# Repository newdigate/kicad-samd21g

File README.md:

# kicad-samd21g
generic samd21g18a board based on arduino mkrzero

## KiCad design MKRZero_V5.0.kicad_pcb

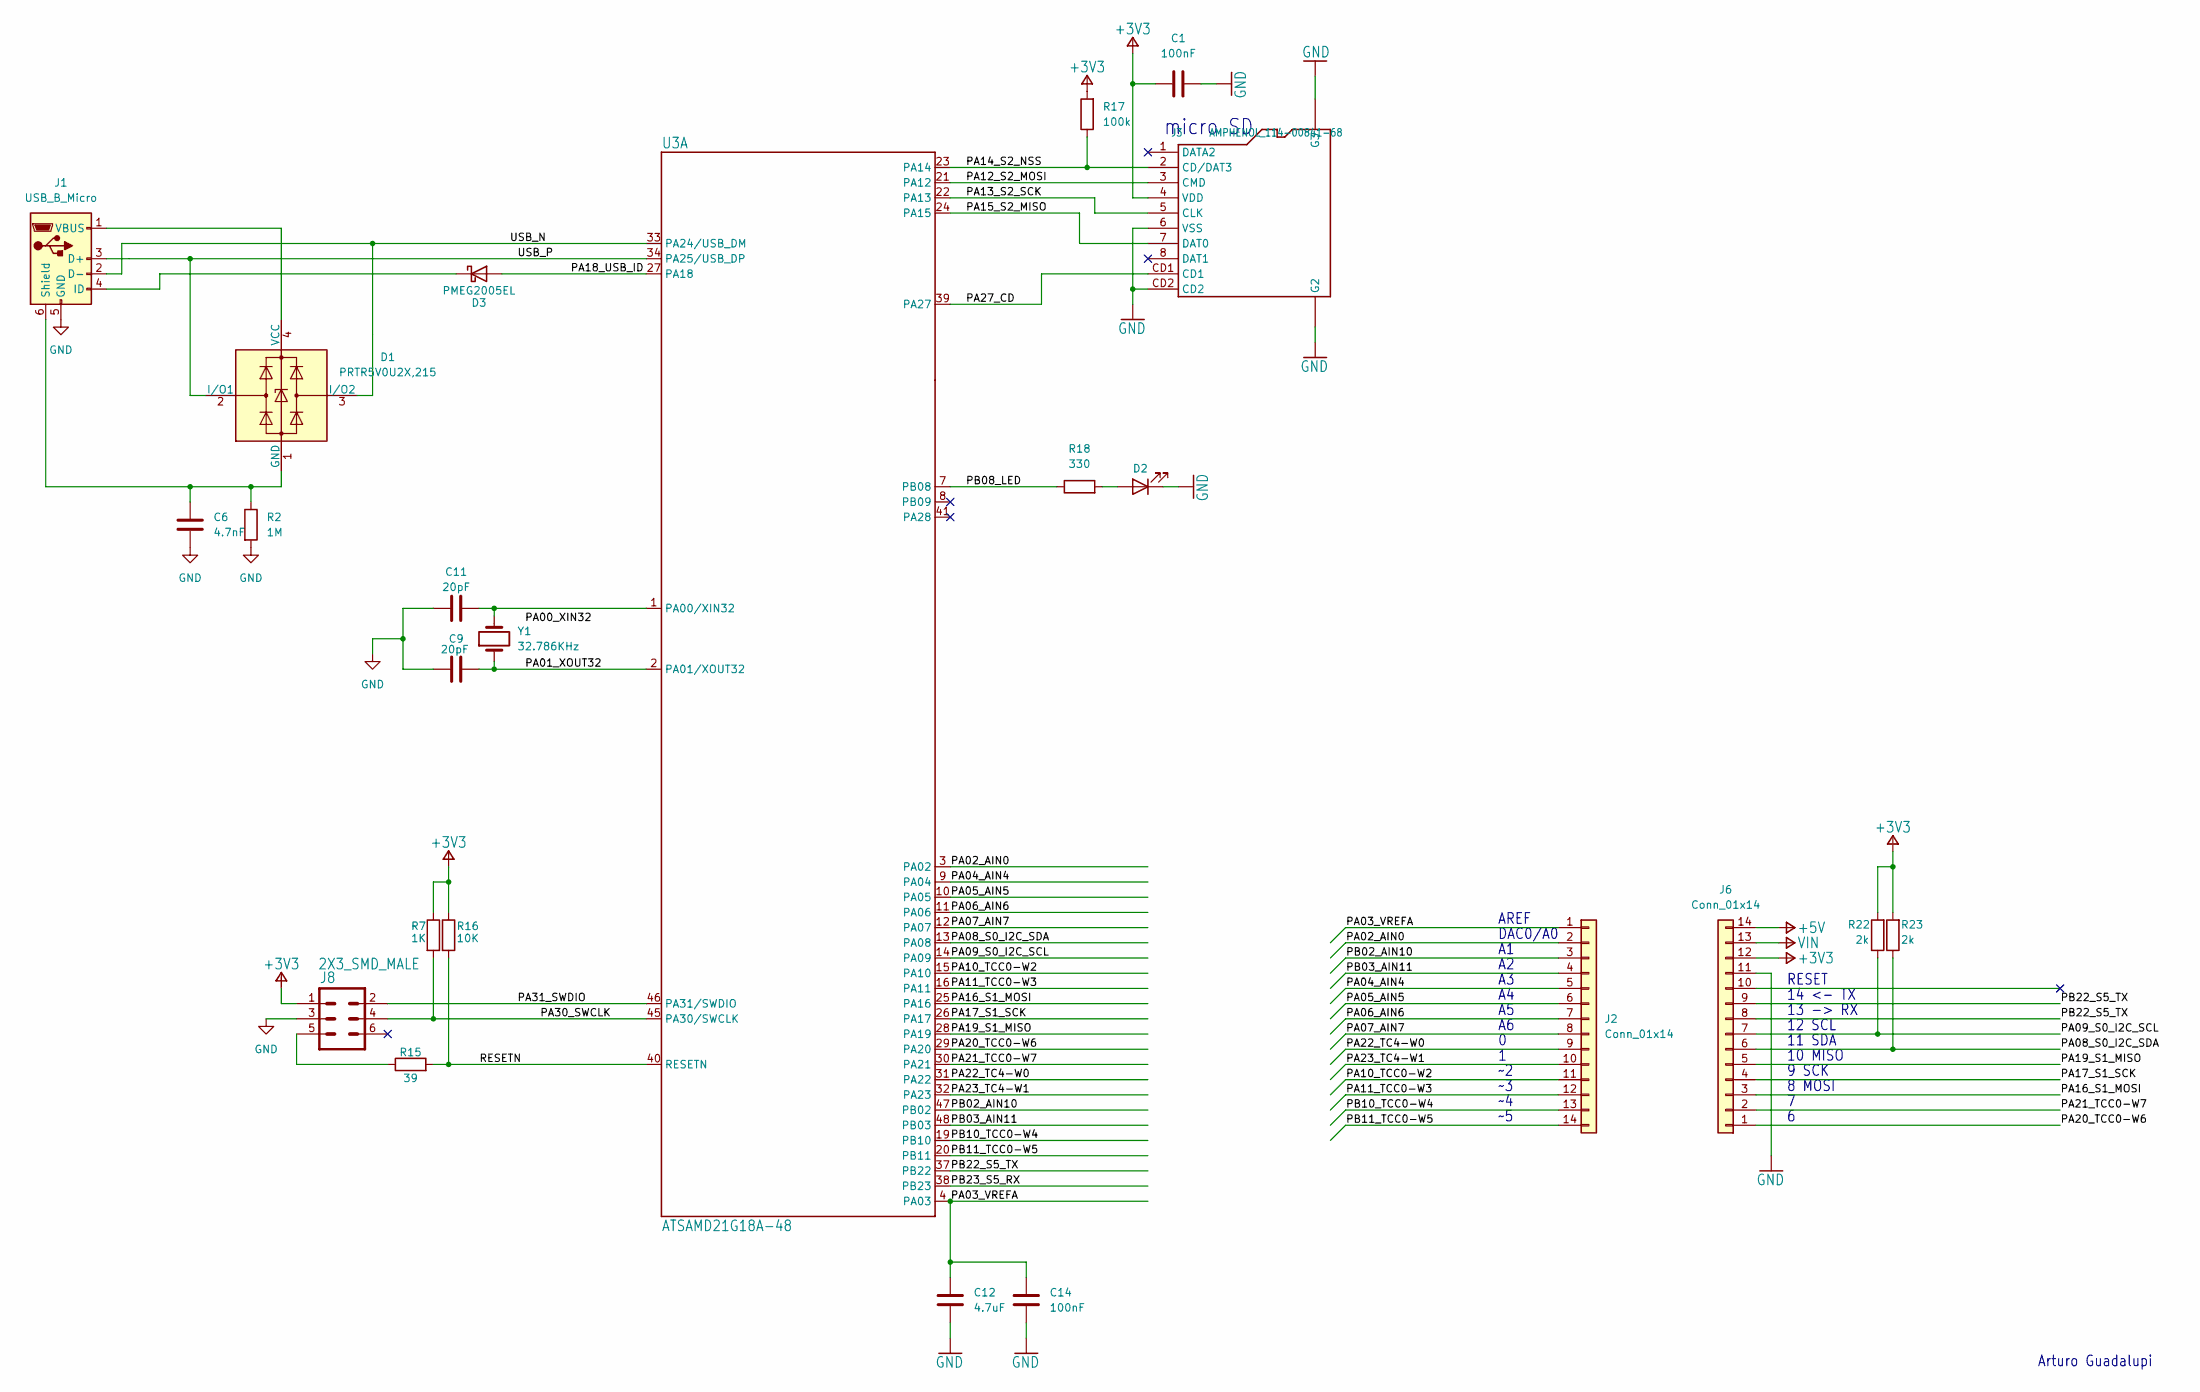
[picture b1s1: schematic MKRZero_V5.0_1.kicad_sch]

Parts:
C1, C14: 100nF; C_0402_1005Metric
C6: 4.7nF; C_0805_2012Metric
C9, C11: 20pF; C_0402_1005Metric
C12: 4.7uF; C_0402_1005Metric
D1: PRTR5V0U2X,215; SOT-143
D2: LED; LED_0603_1608Metric
D3: PMEG2005EL; D_SOD-323
J1: USB_B_Micro; USB_Micro-B_Molex_47346-0001
J2, J6: Conn_01x14; PinHeader_1x14_P2.54mm_Vertical
J3: AMPHENOL_114-00841-68
J8: 2X3_SMD_MALE; 2X3_SMT
R2: 1M; R_0402_1005Metric
R7: 1K; R_0402_1005Metric
R15: 39; R_0402_1005Metric
R16: 10K; R_0402_1005Metric
R17: 100k; R_0402_1005Metric
R18: 330; R_0402_1005Metric
R22, R23: 2k; R_0402_1005Metric
U3: ATSAMD21G18A-48; QFN-48-1EP_7x7mm_P0.5mm_EP5.15x5.15mm
Y1: 32.786KHz; Crystal_SMD_3215-2Pin_3.2x1.5mm

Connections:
+3V3: C1.1, J3.4 (VDD), J6.12, J8.1, R7.1, R16.1, R17.2, R22.2, R23.2; also elsewhere on the board
+5V: J6.14; also elsewhere on the board
/MKRZero_V5.0_1/PA01_XOUT32: C9.2, U3.2 (PA01/XOUT32), Y1.1
/MKRZero_V5.0_1/PA02_AIN0: J2.2, U3.3 (PA02)
/MKRZero_V5.0_1/PA03_VREFA: C12.2, C14.2, J2.1, U3.4 (PA03)
/MKRZero_V5.0_1/PA04_AIN4: J2.5, U3.9 (PA04)
/MKRZero_V5.0_1/PA05_AIN5: J2.6, U3.10 (PA05)
/MKRZero_V5.0_1/PA06_AIN6: J2.7, U3.11 (PA06)
/MKRZero_V5.0_1/PA07_AIN7: J2.8, U3.12 (PA07)
/MKRZero_V5.0_1/PA08_S0_I2C_SDA: J6.6, R23.1, U3.13 (PA08)
/MKRZero_V5.0_1/PA09_S0_I2C_SCL: J6.7, R22.1, U3.14 (PA09)
/MKRZero_V5.0_1/PA10_TCC0-W2: J2.11, U3.15 (PA10)
/MKRZero_V5.0_1/PA11_TCC0-W3: J2.12, U3.16 (PA11)
/MKRZero_V5.0_1/PA12_S2_MOSI: J3.3 (CMD), U3.21 (PA12)
/MKRZero_V5.0_1/PA13_S2_SCK: J3.5 (CLK), U3.22 (PA13)
/MKRZero_V5.0_1/PA14_S2_NSS: J3.2 (CD/DAT3), R17.1, U3.23 (PA14)
/MKRZero_V5.0_1/PA15_S2_MISO: J3.7 (DAT0), U3.24 (PA15)
/MKRZero_V5.0_1/PA16_S1_MOSI: J6.3, U3.25 (PA16)
/MKRZero_V5.0_1/PA17_S1_SCK: J6.4, U3.26 (PA17)
/MKRZero_V5.0_1/PA18_USB_ID: D3.2 (A), U3.27 (PA18)
/MKRZero_V5.0_1/PA19_S1_MISO: J6.5, U3.28 (PA19)
/MKRZero_V5.0_1/PA20_TCC0-W6: J6.1, U3.29 (PA20)
/MKRZero_V5.0_1/PA21_TCC0-W7: J6.2, U3.30 (PA21)
/MKRZero_V5.0_1/PA22_TC4-W0: J2.9, U3.31 (PA22)
/MKRZero_V5.0_1/PA23_TC4-W1: J2.10, U3.32 (PA23)
/MKRZero_V5.0_1/PA27_CD: J3.CD1, U3.39 (PA27)
/MKRZero_V5.0_1/PA30_SWCLK: J8.4, R7.2, U3.45 (PA30/SWCLK)
/MKRZero_V5.0_1/PA31_SWDIO: J8.2, U3.46 (PA31/SWDIO)
/MKRZero_V5.0_1/PB02_AIN10: J2.3, U3.47 (PB02)
/MKRZero_V5.0_1/PB03_AIN11: J2.4, U3.48 (PB03)
/MKRZero_V5.0_1/PB08_LED: R18.1, U3.7 (PB08)
/MKRZero_V5.0_1/PB10_TCC0-W4: J2.13, U3.19 (PB10)
/MKRZero_V5.0_1/PB11_TCC0-W5: J2.14, U3.20 (PB11)
/MKRZero_V5.0_1/PB22_S5_TX: J6.8, J6.9, U3.37 (PB22)
/MKRZero_V5.0_1/PB23_S5_RX: U3.38 (PB23)
/MKRZero_V5.0_1/RESETN: R15.2, R16.2, U3.40 (RESETN)
/MKRZero_V5.0_1/USB_N: D1.3 (I/O2), J1.2 (D-), U3.33 (PA24/USB_DM)
/MKRZero_V5.0_1/USB_P: D1.2 (I/O1), J1.3 (D+), U3.34 (PA25/USB_DP)
GND: C1.2, C6.2, C9.1, C11.1, C12.1, C14.1, D2.1 (K), J1.5 (GND), J3.6 (VSS), J3.CD2, J3.SH1 (G3), J3.SH2 (G3), J3.SH3 (G2), J3.SH4 (G2), J6.11, J8.3, R2.2; also elsewhere on the board
unnamed: C6.1, D1.1 (GND), J1.6 (Shield), R2.1
unnamed: D1.4 (VCC), J1.1 (VBUS)
unnamed: D2.2 (A), R18.2
unnamed: D3.1 (K), J1.4 (ID)
unnamed: J8.5, R15.1
unnamed: C11.2, U3.1 (PA00/XIN32), Y1.2
VIN: J6.13

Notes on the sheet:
8 MOSI
AREF
micro SD
12 SCL
RESET
Arturo Guadalupi
10 MISO
DAC0/A0
13 -> RX
14 <- TX
9 SCK
11 SDA

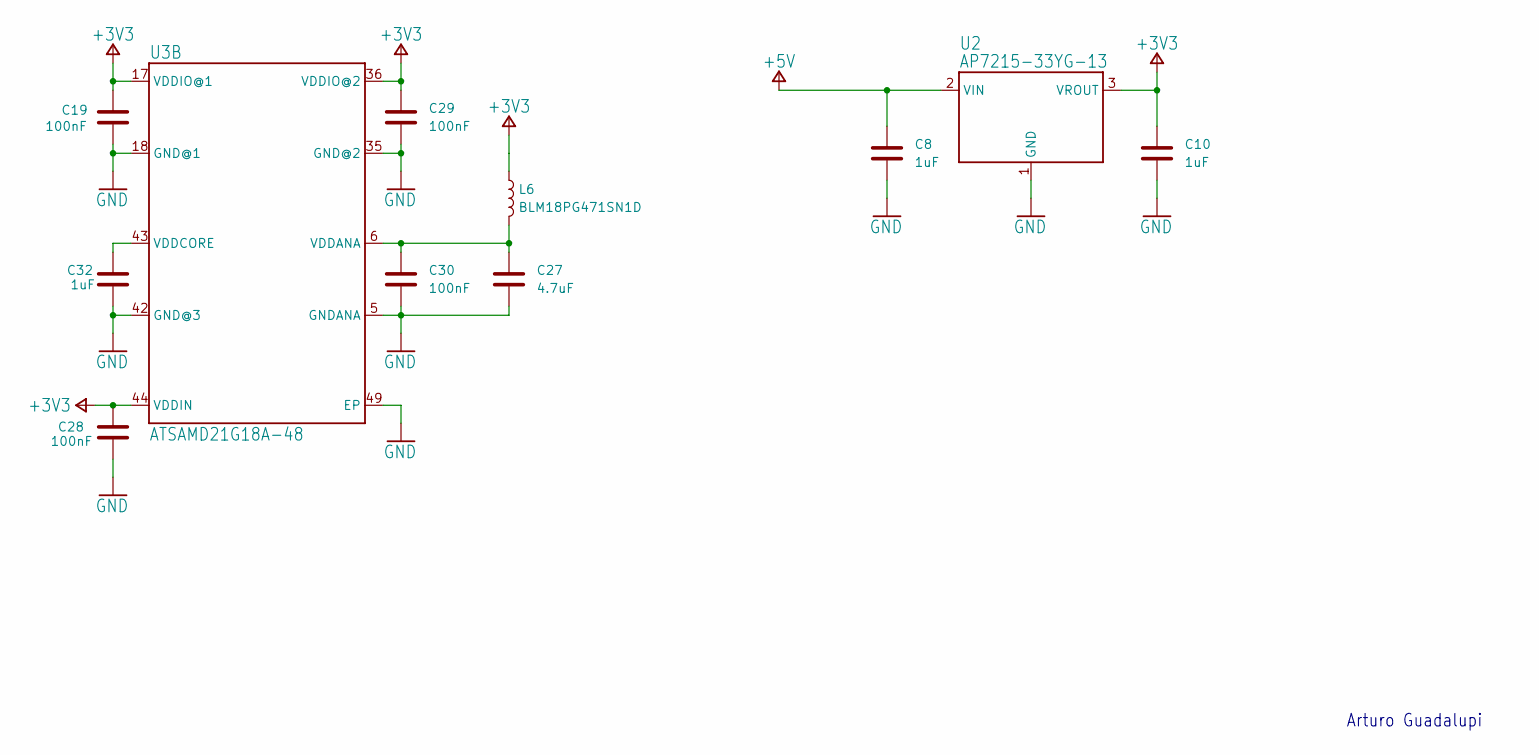
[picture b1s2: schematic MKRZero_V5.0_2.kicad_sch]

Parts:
C8, C10, C32: 1uF; C_0402_1005Metric
C19, C28, C29, C30: 100nF; C_0402_1005Metric
C27: 4.7uF; C_0402_1005Metric
L6: BLM18PG471SN1D; L_0603_1608Metric
U2: AP7215-33YG-13; SOT-89-3
U3: ATSAMD21G18A-48; QFN-48-1EP_7x7mm_P0.5mm_EP5.15x5.15mm

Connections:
+3V3: C10.2, C19.1, C28.1, C29.2, L6.1, U2.3 (VROUT), U3.17 (VDDIO@1), U3.36 (VDDIO@2), U3.44 (VDDIN); also elsewhere on the board
+5V: C8.2, U2.2 (VIN); also elsewhere on the board
GND: C8.1, C10.1, C19.2, C27.2, C28.2, C29.1, C30.2, C32.2, U2.1 (GND), U3.5 (GNDANA), U3.18 (GND@1), U3.35 (GND@2), U3.42 (GND@3), U3.49 (EP); also elsewhere on the board
unnamed: C27.1, C30.1, L6.2, U3.6 (VDDANA)
unnamed: C32.1, U3.43 (VDDCORE)

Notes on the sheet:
Arturo Guadalupi

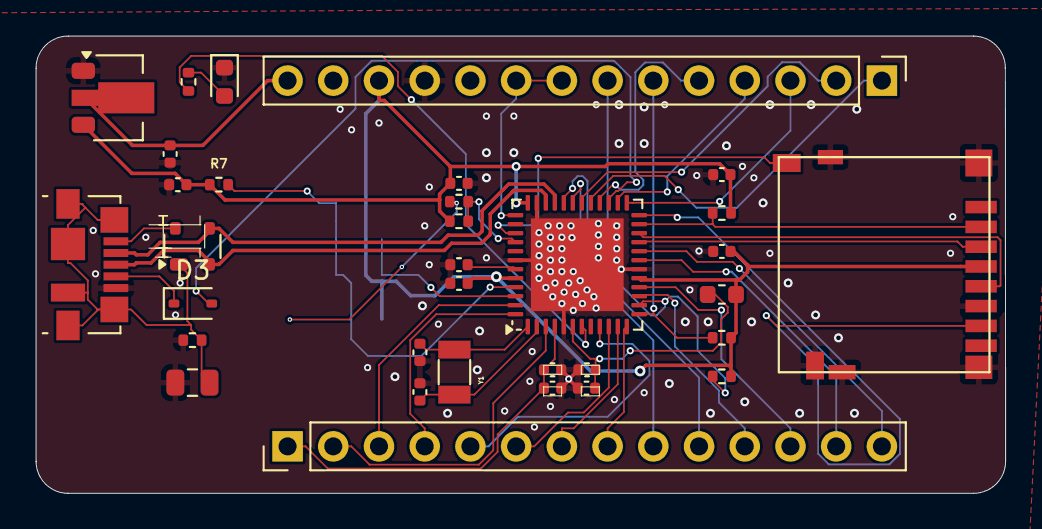
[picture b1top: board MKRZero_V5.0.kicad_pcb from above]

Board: 2 copper layers, 53.9 x 25.4 mm, 34 parts (1 on the bottom side), 46 nets.

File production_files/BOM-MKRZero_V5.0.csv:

Comment,Designator,Footprint,LCSC
1K,R7,R_0402_1005Metric,C11702
"PRTR5V0U2X,215",D1,SOT-143,C12333
USB_B_Micro,J1,USB_Micro-B_Molex_47346-0001,C132560
32.786KHz,Y1,Crystal_SMD_3215-2Pin_3.2x1.5mm,C145140
100nF,"C1,C14,C19,C28,C29,C30",C_0402_1005Metric,C1525
20pF,C11,C_0402_1005Metric,C1530
20pF,C9,C_0402_1005Metric,C1554
4.7nF,C6,C_0805_2012Metric,C1744
LED,D2,LED_0603_1608Metric,C2286
4.7uF,"C12,C27",C_0402_1005Metric,C23733
330,R18,R_0402_1005Metric,C25104
39,R15,R_0402_1005Metric,C25110
100k,R17,R_0402_1005Metric,C25741
10K,R16,R_0402_1005Metric,C25744
1M,R2,R_0402_1005Metric,C26083
AMPHENOL_114-00841-68,J3,AMPHENOL_114-00841-68,C3195424
2k,"R22,R23",R_0402_1005Metric,C4109
AP7215-33YG-13,U2,SOT-89-3,C460367
1uF,"C10,C32,C8",C_0402_1005Metric,C52923
ATSAMD21G18A-48,U3,QFN-48-1EP_7x7mm_P0.5mm_EP5.15x5.15mm,C614475
BLM18PG471SN1D,L6,L_0603_1608Metric,C97853
2X3_SMD_MALE,J8,2X3_SMT,
PMEG2005EL,D3,D_SOD-323,
Conn_01x14,J2,PinHeader_1x14_P2.54mm_Vertical,
Conn_01x14,J6,PinHeader_1x14_P2.54mm_Vertical,
